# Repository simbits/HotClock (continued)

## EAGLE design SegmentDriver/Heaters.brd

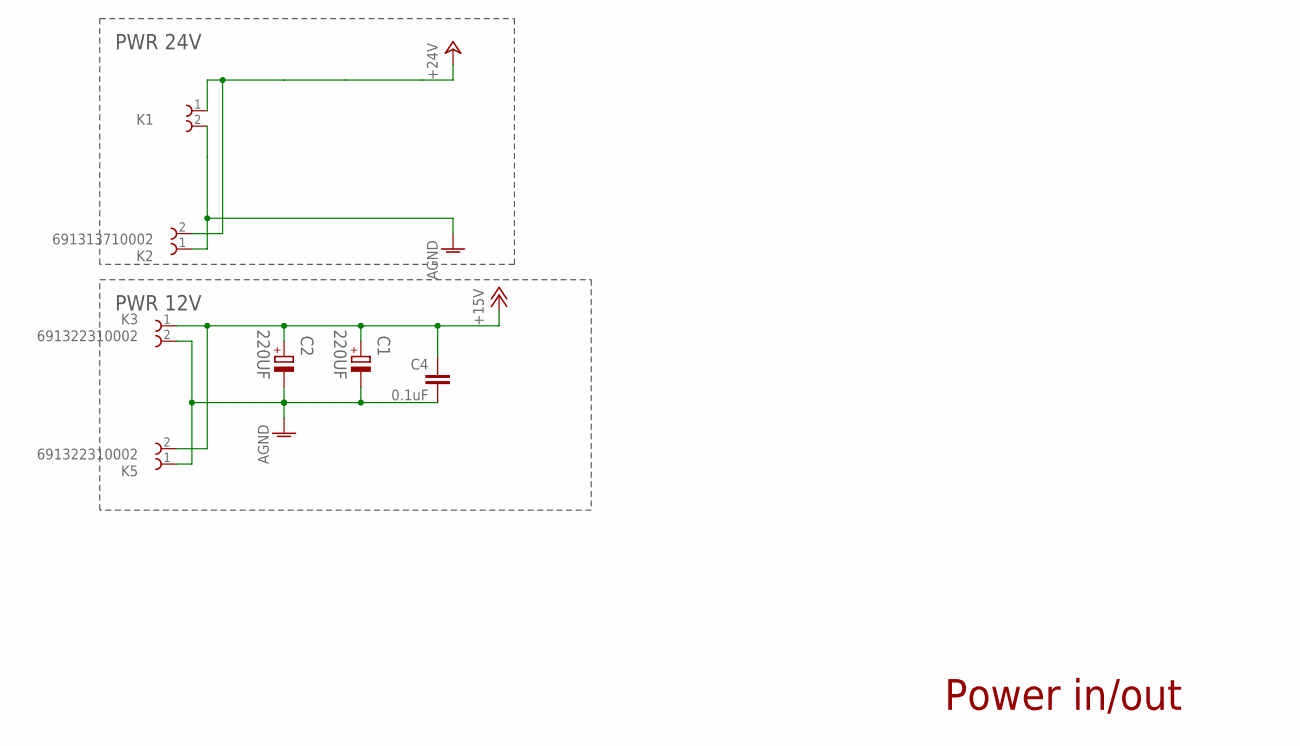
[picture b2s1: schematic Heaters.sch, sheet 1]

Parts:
C1, C2: 220UF; CAPAE830X1050N
C4: 0.1uF; C0603K
K1, K2: 691313710002
K3, K5: 691322310002

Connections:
+15V: C1.1, C2.1, C4.2, K3.1, K5.2; also elsewhere on the board
+24V: K1.1, K2.2; also elsewhere on the board
AGND: C1.2, C2.2, C4.1, K1.2, K2.1, K3.2, K5.1; also elsewhere on the board

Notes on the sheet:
PWR 24V
PWR 12V
Power in/out

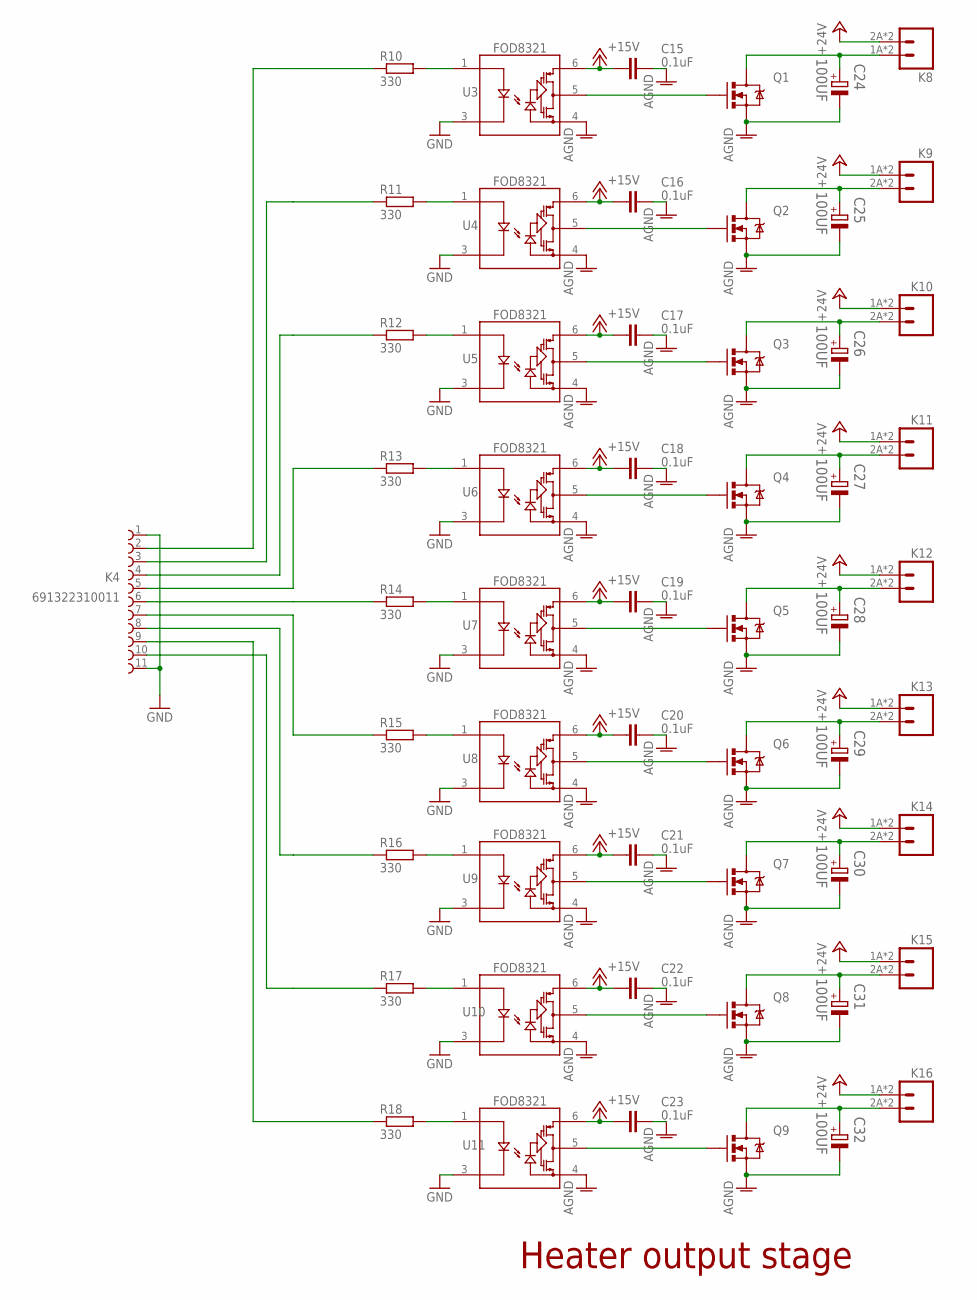
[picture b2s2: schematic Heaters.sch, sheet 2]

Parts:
C15, C16, C17, C18, C19, C20, C21, C22, C23: 0.1uF; C1206K
C24, C25, C26, C27, C28, C29, C30, C31, C32: 100UF; CAPAE1700X1700N
K4: 691322310011
K8, K9, K10, K11, K12, K13, K14, K15, K16: M02-MOLEX-104188-0210; LITE-TRAP-CONNECTOR-2
Q1, Q2, Q3, Q4, Q5, Q6, Q7, Q8, Q9: MOSFET-NCHANNEL-FDMS5672; POWERPACK5060-8
R10, R11, R12, R13, R14, R15, R16, R17, R18: 330; R0603
U3, U4, U5, U6, U7, U8, U9, U10, U11: FOD8321; WB-SOP5

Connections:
+15V: C15.1, C16.1, C17.1, C18.1, C19.1, C20.1, C21.1, C22.1, C23.1, U3.6 (VDD), U4.6 (VDD), U5.6 (VDD), U6.6 (VDD), U7.6 (VDD), U8.6 (VDD), U9.6 (VDD), U10.6 (VDD), U11.6 (VDD); also elsewhere on the board
+24V: K8.2A (2), K8.2B (2), K9.1A (1), K9.1B (1), K10.1A (1), K10.1B (1), K11.1A (1), K11.1B (1), K12.1A (1), K12.1B (1), K13.1A (1), K13.1B (1), K14.1A (1), K14.1B (1), K15.1A (1), K15.1B (1), K16.1A (1), K16.1B (1); also elsewhere on the board
AGND: C15.2, C16.2, C17.2, C18.2, C19.2, C20.2, C21.2, C22.2, C23.2, C24.2, C25.2, C26.2, C27.2, C28.2, C29.2, C30.2, C31.2, C32.2, Q1.S1 (S), Q1.S2 (S), Q1.S3 (S), Q2.S1 (S), Q2.S2 (S), Q2.S3 (S), Q3.S1 (S), Q3.S2 (S), Q3.S3 (S), Q4.S1 (S), Q4.S2 (S), Q4.S3 (S), Q5.S1 (S), Q5.S2 (S), Q5.S3 (S), Q6.S1 (S), Q6.S2 (S), Q6.S3 (S), Q7.S1 (S), Q7.S2 (S), Q7.S3 (S), Q8.S1 (S), Q8.S2 (S), Q8.S3 (S), Q9.S1 (S), Q9.S2 (S), Q9.S3 (S), U3.4 (VSS), U4.4 (VSS), U5.4 (VSS), U6.4 (VSS), U7.4 (VSS), U8.4 (VSS), U9.4 (VSS), U10.4 (VSS), U11.4 (VSS); also elsewhere on the board
GND: K4.1, K4.11, U3.3 (K), U4.3 (K), U5.3 (K), U6.3 (K), U7.3 (K), U8.3 (K), U9.3 (K), U10.3 (K), U11.3 (K)
unnamed: R18.2, U11.1 (A)
unnamed: R17.2, U10.1 (A)
unnamed: C24.1, K8.1A (1), K8.1B (1), Q1.D5 (D), Q1.D6 (D), Q1.D7 (D), Q1.D8 (D), Q1.DPAD (D)
unnamed: R11.2, U4.1 (A)
unnamed: C25.1, K9.2A (2), K9.2B (2), Q2.D5 (D), Q2.D6 (D), Q2.D7 (D), Q2.D8 (D), Q2.DPAD (D)
unnamed: R12.2, U5.1 (A)
unnamed: C26.1, K10.2A (2), K10.2B (2), Q3.D5 (D), Q3.D6 (D), Q3.D7 (D), Q3.D8 (D), Q3.DPAD (D)
unnamed: R13.2, U6.1 (A)
unnamed: R10.2, U3.1 (A)
unnamed: C27.1, K11.2A (2), K11.2B (2), Q4.D5 (D), Q4.D6 (D), Q4.D7 (D), Q4.D8 (D), Q4.DPAD (D)
unnamed: R14.2, U7.1 (A)
unnamed: C28.1, K12.2A (2), K12.2B (2), Q5.D5 (D), Q5.D6 (D), Q5.D7 (D), Q5.D8 (D), Q5.DPAD (D)
unnamed: R15.2, U8.1 (A)
unnamed: C29.1, K13.2A (2), K13.2B (2), Q6.D5 (D), Q6.D6 (D), Q6.D7 (D), Q6.D8 (D), Q6.DPAD (D)
unnamed: R16.2, U9.1 (A)
unnamed: C30.1, K14.2A (2), K14.2B (2), Q7.D5 (D), Q7.D6 (D), Q7.D7 (D), Q7.D8 (D), Q7.DPAD (D)
unnamed: C31.1, K15.2A (2), K15.2B (2), Q8.D5 (D), Q8.D6 (D), Q8.D7 (D), Q8.D8 (D), Q8.DPAD (D)
unnamed: C32.1, K16.2A (2), K16.2B (2), Q9.D5 (D), Q9.D6 (D), Q9.D7 (D), Q9.D8 (D), Q9.DPAD (D)
PWM_DOT1: K4.10, R17.1
PWM_DOT2: K4.9, R18.1
PWM_SEG1: K4.2, R10.1
PWM_SEG2: K4.3, R11.1
PWM_SEG3: K4.4, R12.1
PWM_SEG4: K4.5, R13.1
PWM_SEG5: K4.6, R14.1
PWM_SEG6: K4.7, R15.1
PWM_SEG7: K4.8, R16.1
VO: Q1.G4 (G), U3.5 (VO)
VO1: Q2.G4 (G), U4.5 (VO)
VO2: Q3.G4 (G), U5.5 (VO)
VO3: Q4.G4 (G), U6.5 (VO)
VO4: Q5.G4 (G), U7.5 (VO)
VO5: Q6.G4 (G), U8.5 (VO)
VO6: Q7.G4 (G), U9.5 (VO)
VO7: Q9.G4 (G), U11.5 (VO)
VO8: Q8.G4 (G), U10.5 (VO)

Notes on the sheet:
Heater output stage

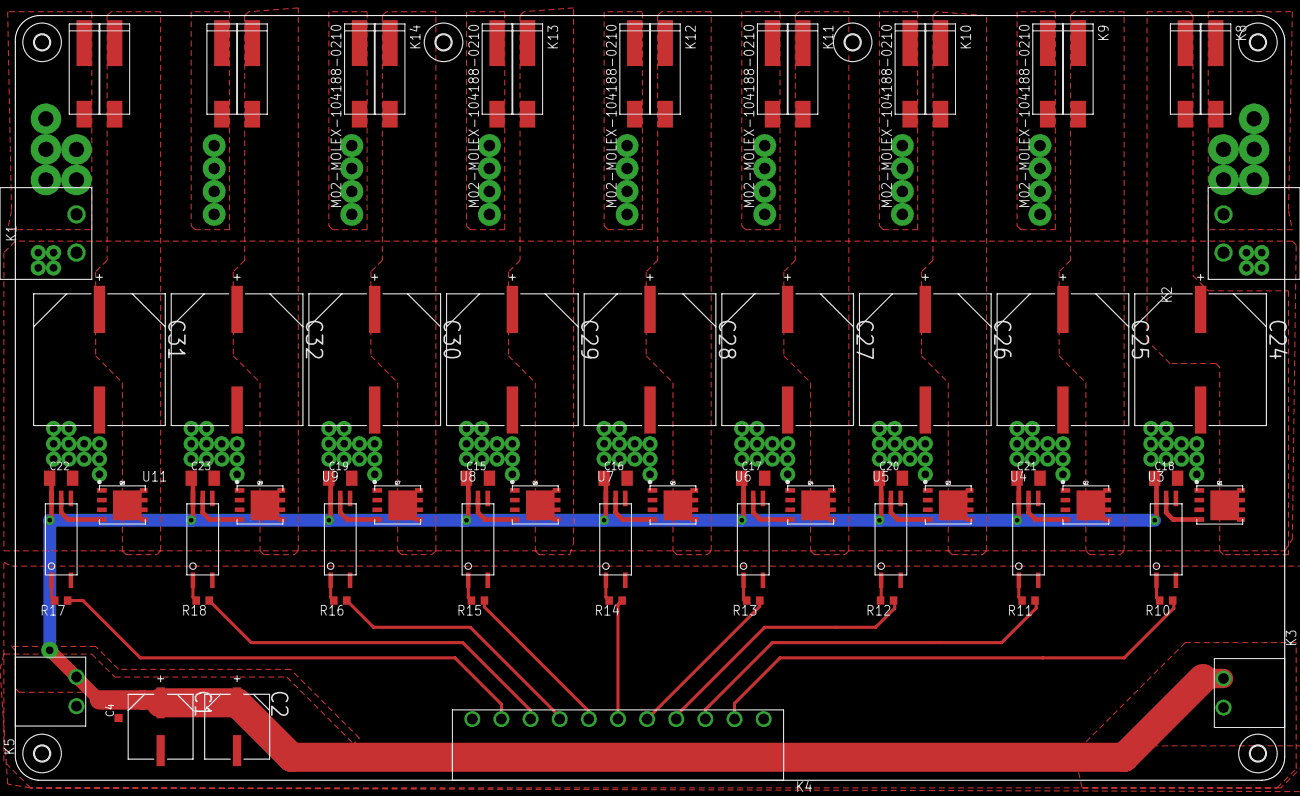
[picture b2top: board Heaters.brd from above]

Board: 2 copper layers, 166.0 x 100.0 mm, 68 parts (0 on the bottom side), 40 nets.

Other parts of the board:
$2_206_$_2016-11-07_20-18-07: MOUNT-HOLE2.0; 2,0
H1, H2, H6, H7, H8: MOUNT-HOLE2.0; 2,0

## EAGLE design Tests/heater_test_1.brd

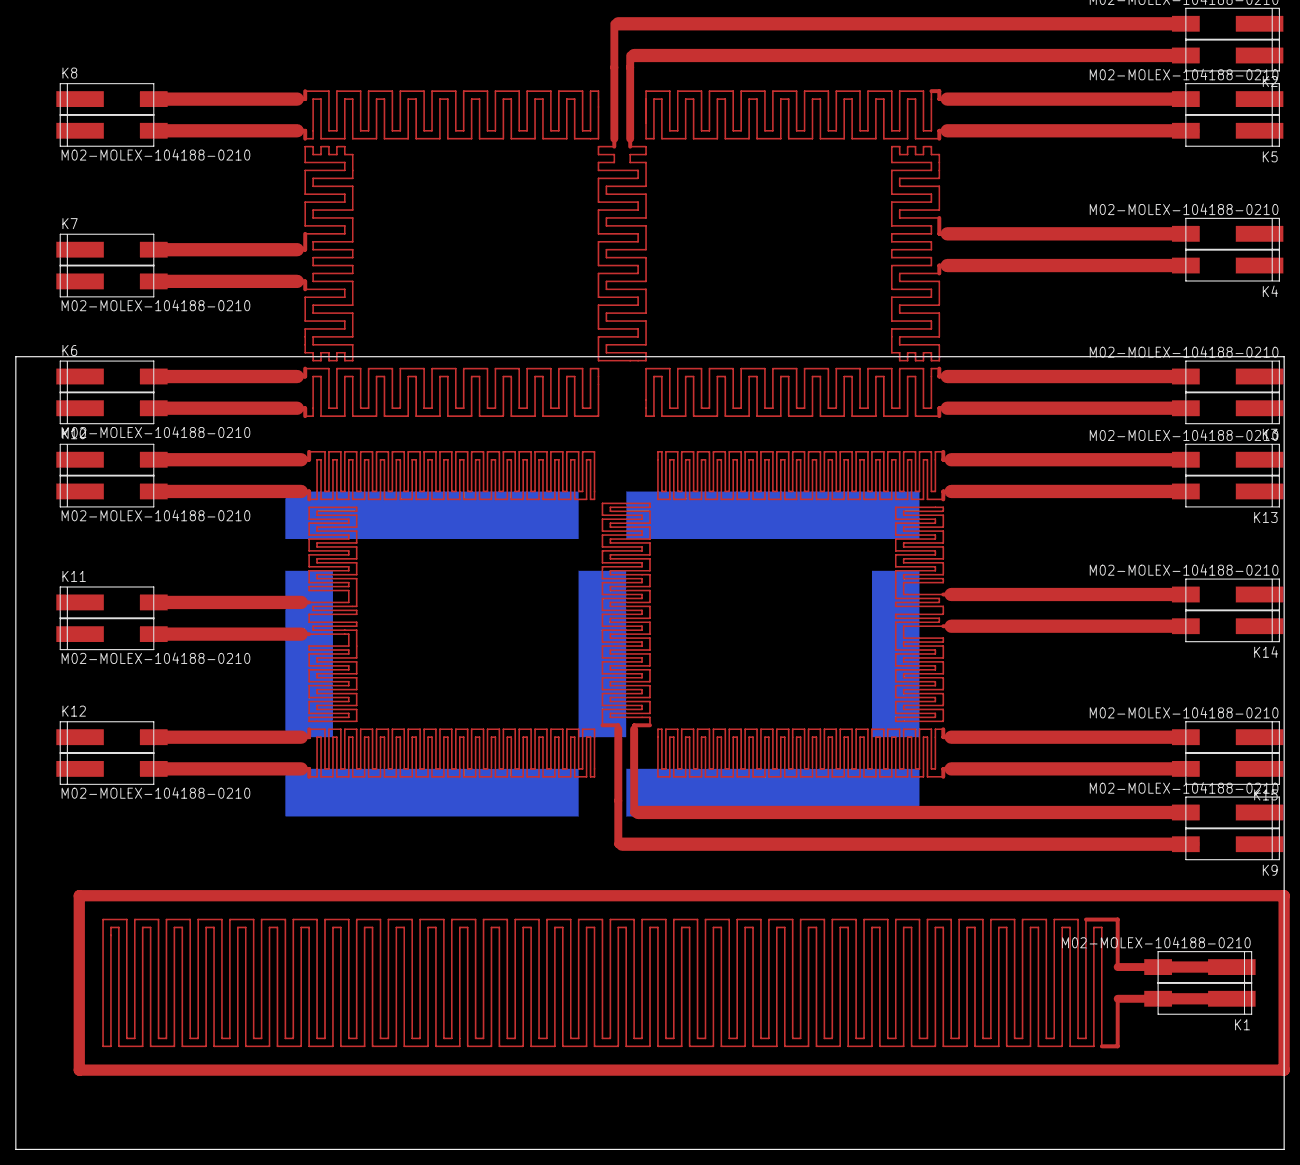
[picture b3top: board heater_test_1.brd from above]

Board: 2 copper layers, 15 parts (0 on the bottom side), 15 nets.

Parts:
K1, K2, K3, K4, K5, K6, K7, K8, K9, K10, K11, K12, K13, K14, K15: M02-MOLEX-104188-0210; LITE-TRAP-CONNECTOR-2

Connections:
H_N: K1.1A, K1.1B, K1.2A, K1.2B
unnamed: K2.1A, K2.1B, K2.2A, K2.2B
unnamed: K3.1A, K3.1B, K3.2A, K3.2B
unnamed: K4.1A, K4.1B, K4.2A, K4.2B
unnamed: K5.1A, K5.1B, K5.2A, K5.2B
unnamed: K6.1A, K6.1B, K6.2A, K6.2B
unnamed: K7.1A, K7.1B, K7.2A, K7.2B
unnamed: K8.1A, K8.1B, K8.2A, K8.2B
unnamed: K9.1A, K9.1B, K9.2A, K9.2B
unnamed: K10.1A, K10.1B, K10.2A, K10.2B
unnamed: K11.1A, K11.1B, K11.2A, K11.2B
unnamed: K12.1A, K12.1B, K12.2A, K12.2B
unnamed: K13.1A, K13.1B, K13.2A, K13.2B
unnamed: K14.1A, K14.1B, K14.2A, K14.2B
unnamed: K15.1A, K15.1B, K15.2A, K15.2B

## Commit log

2016-11-01 Implemented RTD and RS485
2016-11-03 Added ext. gpio, 7 seg. driver, differential filtering
2016-11-03 reduced size to 175mm
2016-11-08 routing rtd inputs
2016-11-08 small repositioning
2016-11-09 RTD AD layout, brd and sch remade consistent
2016-11-11 added power rails
2016-11-11 gpio connections
2016-11-12 schematics finished (probably)
2016-11-23 Seperation of heaters and drivers
2016-11-24 using teensy 3.6
